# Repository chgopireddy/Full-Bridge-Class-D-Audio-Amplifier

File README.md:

# Full-Bridge-Class-D-Audio-Amplifier
LTspice Model for Full Bridge Class D and  Voltage Mode Control, Peak Current Mode Control(PCMC)

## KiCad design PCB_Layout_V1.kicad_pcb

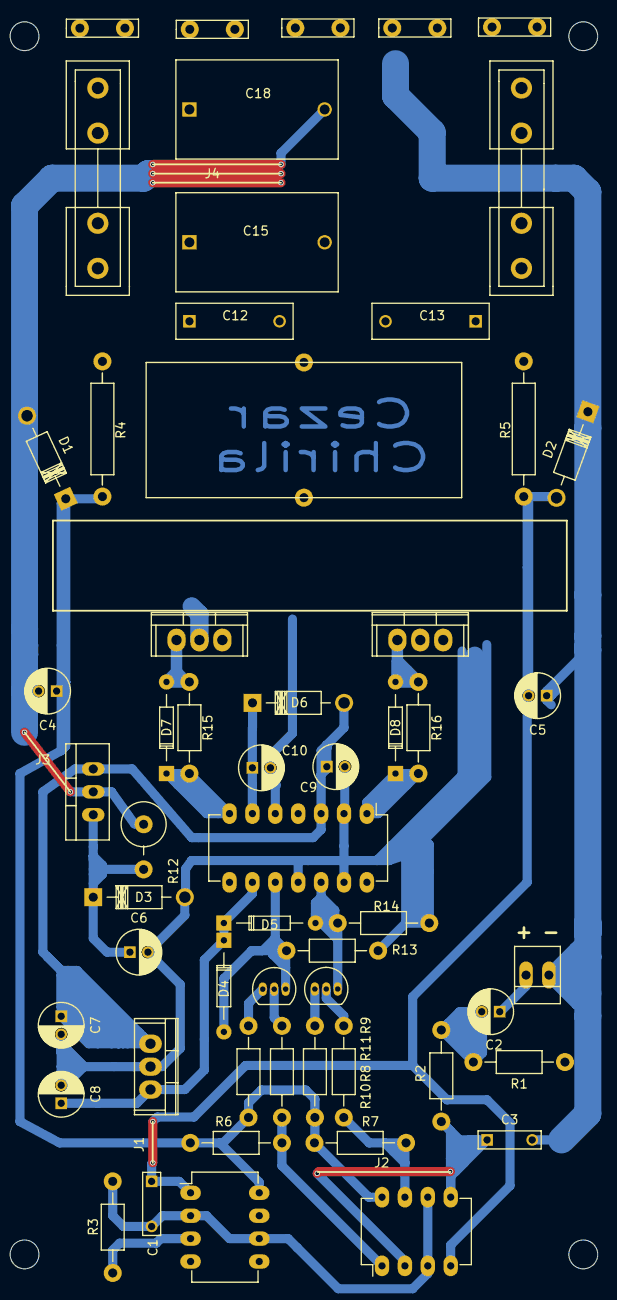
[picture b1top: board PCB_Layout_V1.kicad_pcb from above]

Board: 2 copper layers, 57 parts (1 on the bottom side), 30 nets.

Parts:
C1, C3: 1n; C_Rect_L7_W2_P5
C2: 10uF; C_Radial_D5_L11_P2
C4, C5, C6, C7, C8, C9: 47uF; C_Radial_D5_L11_P2
C10: 22uF; C_Radial_D5_L11_P2
C11: 100n; C_0805_HandSoldering
C12, C13: 220n; C_Rect_L13_W4_P10
C15, C18: 470nF; C_Rect_L18_W11_H19_P15
D1, D2: 5V1; Diode_DO-41_SOD81_Horizontal_RM10
D3: 12V; Diode_DO-41_SOD81_Horizontal_RM10
D4, D5, D7, D8: 1N4148; Diode_DO-35_SOD27_Horizontal_RM10
D6: MUR120; Diode_DO-41_SOD81_Horizontal_RM10
F1, F2: 6A; Fuseholder5x20_horiz_open_inline_Type-I
L1: 22uH; Inductor_T106-2
P1: Input; PINHEAD1-2
P2, P6: GND; Blade_Conn
P3: +30; Blade_Conn
P4: -30; Blade_Conn
P5: OUT; Blade_Conn
Q1, Q2: 2N5401; TO-92_Inline_Narrow_Oval
Q3: BD241C; TO-220_Neutral123_Vertical
Q4, Q5: IRF540N; TO-220
R1: 330k; Resistor_Horizontal_RM10mm
R2: 2k2; Resistor_Horizontal_RM10mm
R3: 3.3k; Resistor_Horizontal_RM10mm
R4, R5: 1K-2W; Resistor_Horizontal_RM15mm
R6, R7, R8, R9: 1k; Resistor_Horizontal_RM10mm
R10, R11: 10k; Resistor_Horizontal_RM10mm
R12: 10k; Resistor_Vertical_RM5mm
R13, R14: 6.8k; Resistor_Horizontal_RM10mm
R15, R16: 10; Resistor_Horizontal_RM10mm
U1: LMC555CN; DIP-8_W7.62mm_LongPads
U2: LM393; DIP-8_W7.62mm_LongPads
U3: LM7805CT; TO-220
U4: IR2110; DIP-14_W7.62mm_LongPads

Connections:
+5V: C4.1, D1.1, R4.2, R6.1, R7.1, R10.2, R11.2, U1.8, U2.8
+5V_2: C8.1, D4.1, D5.1, U3.3, U4.9
+12V: C7.1, C9.1, D6.2, Q3.3, U3.1, U4.3
+30V: C12.1, F1.2, Q4.2, R4.1
-5V: C1.1, C5.2, D2.2, R5.2, U1.1, U2.4
-30V: C6.2, C7.2, C8.2, C9.2, C13.1, D3.2, F2.2, Q5.3, R5.1, R13.2, R14.2, U3.2, U4.2, U4.11, U4.13
GND: C3.2, C4.2, C5.1, C12.2, C13.2, C15.2, C18.2, D1.2, D2.1, P1.1, P2.1, P6.1, Q3.2, R1.1, R12.1
unnamed: C2.1, R1.2, R2.2
unnamed: C2.2, P1.2
unnamed: C3.1, R2.1, U2.2, U2.5
unnamed: C6.1, D3.1, Q3.1, R12.2
unnamed: C10.1, C11.1, D6.1, U4.6
unnamed: C10.2, C11.2, L1.1, Q4.3, Q5.2, U4.5
unnamed: C15.1, C18.1, L1.2, P5.1
unnamed: D4.2, Q1.3, R13.1, U4.10
unnamed: D5.2, Q2.3, R14.1, U4.12
unnamed: D7.1, R15.2, U4.7
unnamed: D7.2, Q4.1, R15.1
unnamed: D8.1, R16.2, U4.1
unnamed: D8.2, Q5.1, R16.1
unnamed: F1.1, P3.1
unnamed: F2.1, P4.1
unnamed: Q1.1, R10.1
unnamed: Q1.2, R8.1
unnamed: Q2.1, R11.1
unnamed: Q2.2, R9.1
unnamed: R3.1, U1.3
unnamed: R6.2, R8.2, U2.1
unnamed: R7.2, R9.2, U2.7
triangle: C1.2, R3.2, U1.2, U1.6, U2.3, U2.6

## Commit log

2019-09-15 Peak Current Mode control, Buck converter
2019-09-15 Voltage Mode Control, Buck Converter
2019-09-15 Open loop Buck Converter
2019-09-15 Voltage Mode Control using Analog PWM
2019-09-15 Full Bridge Class D Audio Amplifier
2019-09-17 Voltage Mode Control
2019-09-17 Peak Current Mode Control(PCMC)
2019-09-22 Kicad_Files
2019-09-22 Rename PCB_Layout_V1.kicad_pcb to PCB_Layout.kicad_pcb
2019-09-22 Rename PCB_Layout_V2.pro to PCB_Layout.pro
2019-09-22 Kicad_File
2019-09-22 Rename PCB_Layout_V2.kicad_pcb to PCB_Layout_V1.kicad_pcb
